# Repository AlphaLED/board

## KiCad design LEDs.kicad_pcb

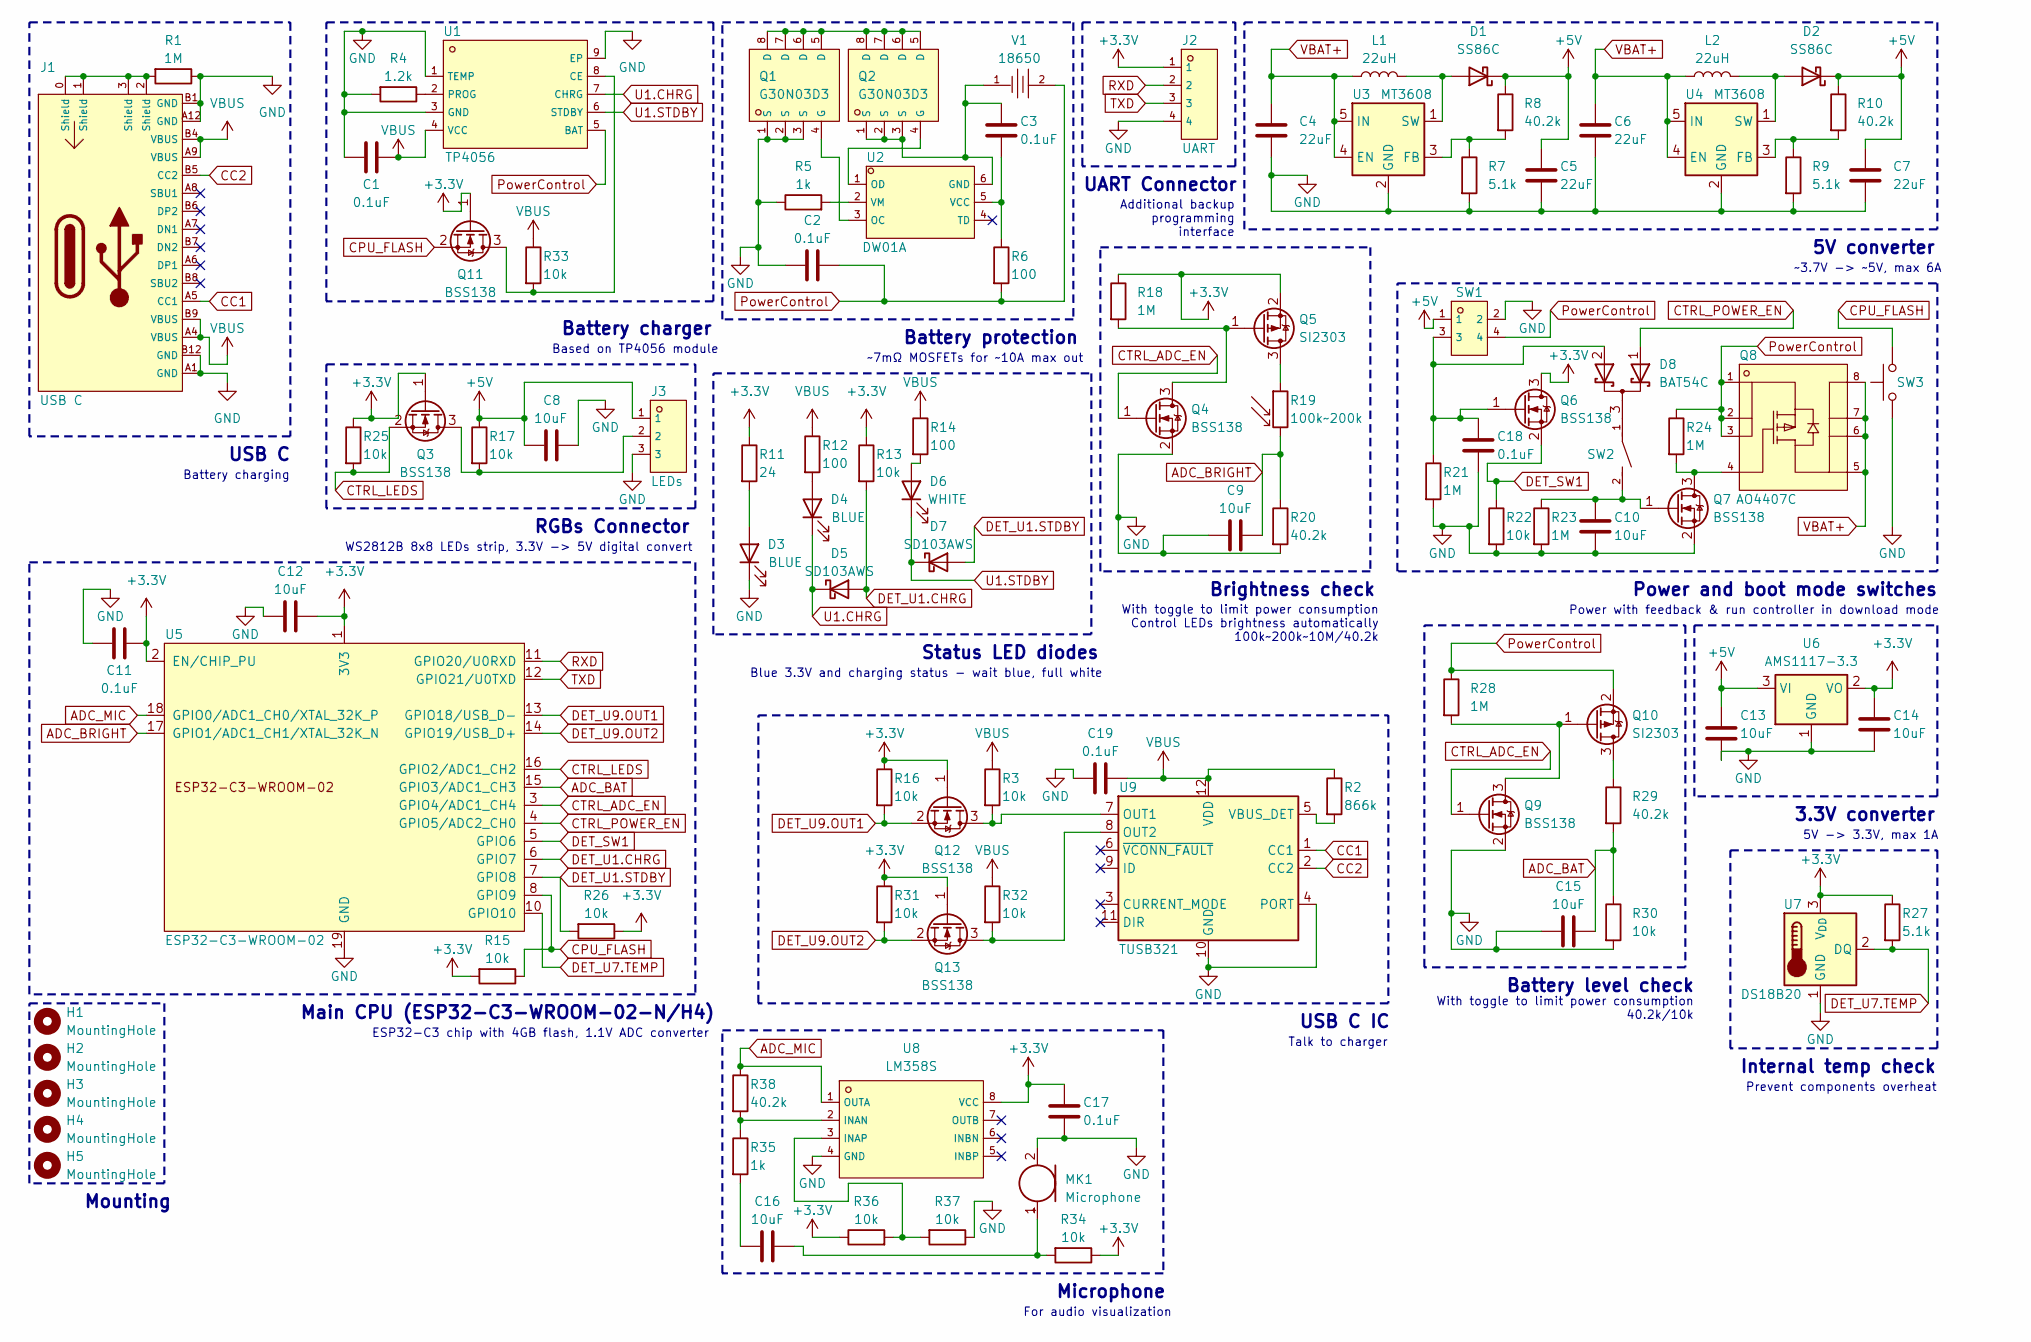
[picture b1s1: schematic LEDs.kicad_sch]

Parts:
C1, C2, C3, C11, C17, C18, C19: 0.1uF; C_0402_1005Metric_Pad0.74x0.62mm_HandSolder; LCSC C344189
C4, C5, C6, C7: 22uF; C_0805_2012Metric_Pad1.18x1.45mm_HandSolder; LCSC C98190
C8, C9, C10, C12, C13, C14, C15, C16: 10uF; C_0805_2012Metric_Pad1.18x1.45mm_HandSolder; LCSC C1713
D1, D2: SS86C; D_SMC_Handsoldering; LCSC C382823
D3, D4: BLUE; LED_0603_1608Metric_Pad1.05x0.95mm_HandSolder; LCSC C965807
D5, D7: SD103AWS; D_SOD-323_HandSoldering; LCSC C513472
D6: WHITE; LED_0603_1608Metric_Pad1.05x0.95mm_HandSolder; LCSC C965808
D8: BAT54C; SOT-23; LCSC C2992451
H1, H2, H3, H4: MountingHole; MountingHole_5.3mm_M5
H5: MountingHole; MountingHole_3.2mm_M3
J1: USB C; USB-C_SMD-TYPE-C-31-M-12; LCSC C2927038
J2: UART; HDR-TH_4P-P2.00-V-M; LCSC C541858
J3: LEDs; HDR-TH_3P-P2.54-V-M-1; LCSC C429954
L1, L2: 22uH; L_Bourns-SRN8040_8x8.15mm; LCSC C2942298
MK1: Microphone; MIC-TH_BD6.0_B6027AP383-056; LCSC C5160215
Q1, Q2: G30N03D3; POWERVDFN-8_L3.2-W3.1-P0.65-LS3.3-BL-1; LCSC C840054
Q3, Q4, Q6, Q7, Q9, Q11, Q12, Q13: BSS138; SOT-23; LCSC C347484
Q5, Q10: SI2303; SOT-23; LCSC C545575
Q8: AO4407C; SOP-8_L4.9-W3.9-P1.27-LS6.0-BL; LCSC C469397
R1, R18, R21, R23, R24, R28: 1M; R_0603_1608Metric_Pad0.98x0.95mm_HandSolder; LCSC C103216
R2: 866k; R_0603_1608Metric_Pad0.98x0.95mm_HandSolder; LCSC C5126056
R3, R13, R15, R16, R17, R22, R25, R26, R30, R31, R32, R33, R34, R36, R37: 10k; R_0603_1608Metric_Pad0.98x0.95mm_HandSolder; LCSC C103210
R4: 1.2k; R_0603_1608Metric_Pad0.98x0.95mm_HandSolder; LCSC C2907081
R5, R35: 1k; R_0603_1608Metric_Pad0.98x0.95mm_HandSolder; LCSC C3016283
R6, R12, R14: 100; R_0603_1608Metric_Pad0.98x0.95mm_HandSolder; LCSC C3017758
R7, R9, R27: 5.1k; R_0603_1608Metric_Pad0.98x0.95mm_HandSolder; LCSC C2907114
R8, R10, R20, R29, R38: 40.2k; R_0603_1608Metric_Pad0.98x0.95mm_HandSolder; LCSC C12447
R11: 24; R_0603_1608Metric_Pad0.98x0.95mm_HandSolder; LCSC C3017772
R19: 100k~200k; R_LDR_5.0x4.1mm_P3mm_Vertical; LCSC C125631
SW1: 4-pin; HDR-TH_4P-P2.00-V-M-R2-C2-S2.00; LCSC C6332216
SW2: SW-TH_KF1001-01P-B0-FL-ON-01B; LCSC C5299502
SW3: SW-TH_4P-L4.5-W4.5-P3.00-LS5.0; LCSC C5359331
U1: TP4056; SOP-8_L4.9-W3.9-P1.27-LS6.0-TL-EP; LCSC C7473158
U2: DW01A; SOT-23-6_L2.9-W1.6-P0.95-LS2.8-BL; LCSC C351410
U3, U4: MT3608; SOT-23-6; LCSC C2932326
U5: ESP32-C3-WROOM-02; LCSC C2944070
U6: AMS1117-3.3; SOT-223-3_TabPin2; LCSC C5181460
U7: DS18B20; TO-92_Inline; LCSC C5379069
U8: LM358S; SOP-8_L4.9-W3.9-P1.27-LS6.0-BL; LCSC C83902
U9: TUSB321; Texas_X2QFN-12_1.6x1.6mm_P0.4mm; LCSC C139392
V1: 18650; BAT-TH_BH-18650-A1AJ005; LCSC C5290176

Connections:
+3.3V: C11.2, C12.2, C14.1, C17.1, J2.1, Q3.1 (G), Q5.2 (S), Q6.3 (D), Q11.1 (G), Q12.1 (G), Q13.1 (G), R11.1, R13.1, R15.2, R16.1, R18.1, R25.1, R26.1, R27.1, R31.1, R34.1, R36.1, U5.1 (3V3), U5.2 (EN/CHIP_PU), U6.2 (VO), U7.3 (V_{DD}), U8.8 (VCC)
+5V: C5.1, C7.1, C8.2, C13.1, D1.1 (K), D2.1 (K), J3.1, R8.1, R10.1, R17.1, SW1.1, U6.3 (VI)
ADC_BAT: C15.2, R29.2, R30.1, U5.15 (GPIO3/ADC1_CH3)
ADC_BRIGHT: C9.2, R19.2, R20.1, U5.17 (GPIO1/ADC1_CH1/XTAL_32K_N)
ADC_MIC: R38.1, U5.18 (GPIO0/ADC1_CH0/XTAL_32K_P), U8.1 (OUTA)
CC1: J1.A5 (CC1), U9.1 (CC1)
CC2: J1.B5 (CC2), U9.2 (CC2)
CTRL_ADC_EN: Q4.1 (G), Q9.1 (G), U5.3 (GPIO4/ADC1_CH4)
CTRL_LEDS: Q3.2 (S), R25.2, U5.16 (GPIO2/ADC1_CH2)
CTRL_POWER_EN: D8.1 (K), U5.4 (GPIO5/ADC2_CH0)
DET_SW1: Q6.2 (S), R22.1, U5.5 (GPIO6)
DET_U1.CHRG: D5.2 (A), R13.2, U5.6 (GPIO7)
DET_U1.STDBY: D7.2 (A), R26.2, U5.7 (GPIO8)
DET_U7.TEMP: R27.2, U5.10 (GPIO10), U7.2 (DQ)
DET_U9.OUT1: Q12.2 (S), R16.2, U5.13 (GPIO18/USB_D-)
DET_U9.OUT2: Q13.2 (S), R31.2, U5.14 (GPIO19/USB_D+)
unnamed: C16.2, R35.2
unnamed: D1.2 (A), L1.2, U3.1 (SW)
unnamed: D2.2 (A), L2.2, U4.1 (SW)
unnamed: D3.2 (A), R11.2
unnamed: D4.2 (A), R12.2
unnamed: D6.2 (A), R14.2
unnamed: D8.3 (A), SW2.1
unnamed: J1.0 (Shield), J1.1 (Shield), J1.2 (Shield), J1.3 (Shield), R1.2
unnamed: C16.1, MK1.1 (+), R34.2
unnamed: Q1.5 (D), Q1.6 (D), Q1.7 (D), Q1.8 (D), Q2.5 (D), Q2.6 (D), Q2.7 (D), Q2.8 (D)
unnamed: Q1.4 (G), U2.3 (OC)
unnamed: Q2.4 (G), U2.1 (OD)
unnamed: J3.2, Q3.3 (D), R17.2
unnamed: Q4.3 (D), Q5.1 (G), R18.2
unnamed: Q5.3 (D), R19.1
unnamed: C18.1, D8.2 (K), Q6.1 (G), R21.1, SW1.3
unnamed: Q7.3 (D), Q8.4 (G), R24.2
unnamed: C10.1, Q7.1 (G), R23.1, SW2.2
unnamed: Q10.3 (D), R29.1
unnamed: Q9.3 (D), Q10.1 (G), R28.2
unnamed: Q11.3 (D), R33.2, U1.8 (CE)
unnamed: Q12.3 (D), R3.2, U9.7 (OUT1)
unnamed: Q13.3 (D), R32.2, U9.8 (OUT2)
unnamed: R4.1, U1.2 (PROG)
unnamed: C3.1, Q2.1 (S), Q2.2 (S), Q2.3 (S), U2.6 (GND), V1.1
unnamed: C3.2, R6.1, U2.5 (VCC)
unnamed: R5.2, U2.2 (VM)
unnamed: R7.1, R8.2, U3.3 (FB)
unnamed: R9.1, R10.2, U4.3 (FB)
unnamed: R35.1, R38.2, U8.2 (INAN)
unnamed: R36.2, R37.2, U8.3 (INAP)
unnamed: R2.2, U9.5 (VBUS_DET)
PowerControl: C2.2, Q8.1 (S), Q8.2 (S), Q8.3 (S), Q10.2 (S), R6.2, R24.1, R28.1, SW1.4, U1.5 (BAT), V1.2
RXD: J2.2, U5.11 (GPIO20/U0RXD)
TXD: J2.3, U5.12 (GPIO21/U0TXD)
U1.CHRG: D4.1 (K), D5.1 (K), U1.7 (CHRG)
U1.STDBY: D6.1 (K), D7.1 (K), U1.6 (STDBY)
VBAT+: C4.1, C6.1, L1.1, L2.1, Q8.5 (D), Q8.6 (D), Q8.7 (D), Q8.8 (D), U3.4 (EN), U3.5 (IN), U4.4 (EN), U4.5 (IN)
VBUS: C1.2, C19.2, J1.A4 (VBUS), J1.A9 (VBUS), J1.B4 (VBUS), J1.B9 (VBUS), R2.1, R3.1, R12.1, R14.1, R32.1, R33.1, U1.4 (VCC), U9.12 (VDD)

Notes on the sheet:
Internal temp check
With toggle to limit power consumption Control LEDs brightness automatically 100k~200k~10M/40.2k
USB C
Battery level check
Prevent components overheat
Power with feedback & run controller in download mode
Main CPU (ESP32-C3-WROOM-02-N/H4)
Brightness check
Microphone
Blue 3.3V and charging status - wait blue, full white
WS2812B 8x8 LEDs strip, 3.3V -> 5V digital convert
3.3V converter
RGBs Connector
Battery protection
Status LED diodes
Talk to charger
5V -> 3.3V, max 1A
Battery charging
~7mΩ MOSFETs for ~10A max out
ESP32-C3 chip with 4GB flash, 1.1V ADC converter
Mounting
USB C IC
Power and boot mode switches
5V converter
Battery charger
Based on TP4056 module
UART Connector
Additional backup programming interface
~3.7V -> ~5V, max 6A
With toggle to limit power consumption 40.2k/10k
For audio visualization

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
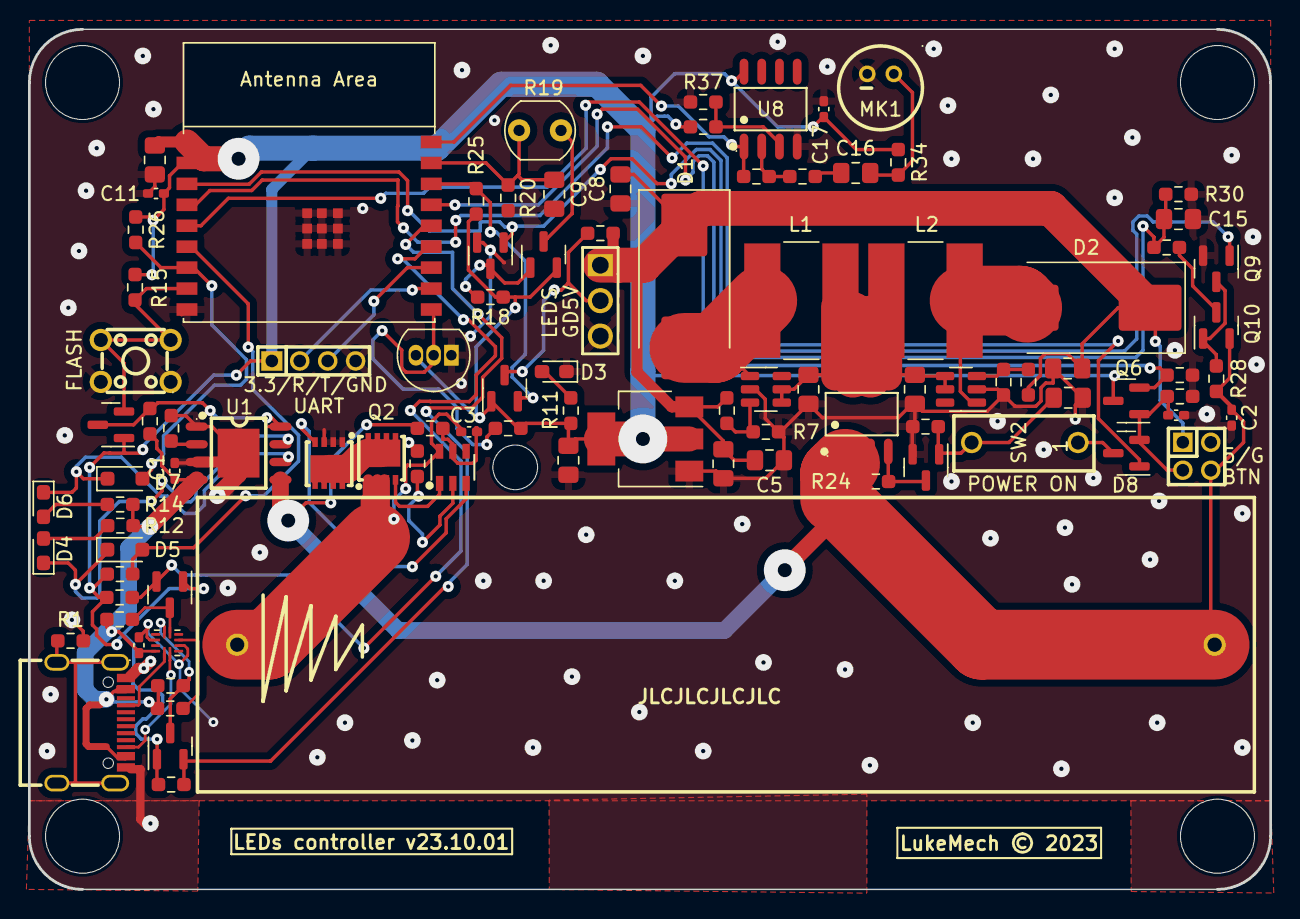
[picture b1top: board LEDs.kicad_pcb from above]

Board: 2 copper layers, 88.9 x 61.6 mm, 102 parts (0 on the bottom side), 57 nets.

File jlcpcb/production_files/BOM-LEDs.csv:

Comment,Designator,Footprint,LCSC
10k,"R13,R15,R16,R17,R22,R25,R26,R3,R30,R31,R32,R33,R34,R36,R37",R_0603_1608Metric_Pad0.98x0.95mm_HandSolder,C103210
1M,"R1,R18,R21,R23,R24,R28",R_0603_1608Metric_Pad0.98x0.95mm_HandSolder,C103216
40.2k,"R10,R20,R29,R38,R8",R_0603_1608Metric_Pad0.98x0.95mm_HandSolder,C12447
100k~200k,R19,R_LDR_5.0x4.1mm_P3mm_Vertical,C125631
TUSB321,U9,Texas_X2QFN-12_1.6x1.6mm_P0.4mm,C139392
10uF,"C10,C12,C13,C14,C15,C16,C8,C9",C_0805_2012Metric_Pad1.18x1.45mm_HandSolder,C1713
1.2k,R4,R_0603_1608Metric_Pad0.98x0.95mm_HandSolder,C2907081
5.1k,"R27,R7,R9",R_0603_1608Metric_Pad0.98x0.95mm_HandSolder,C2907114
USB C,J1,USB-C_SMD-TYPE-C-31-M-12,C2927038
MT3608,"U3,U4",SOT-23-6,C2932326
22uH,"L1,L2",L_Bourns-SRN8040_8x8.15mm,C2942298
ESP32-C3-WROOM-02,U5,ESP32-C3-WROOM-02,C2944070
BAT54C,D8,SOT-23,C2992451
1k,"R35,R5",R_0603_1608Metric_Pad0.98x0.95mm_HandSolder,C3016283
100,"R12,R14,R6",R_0603_1608Metric_Pad0.98x0.95mm_HandSolder,C3017758
24,R11,R_0603_1608Metric_Pad0.98x0.95mm_HandSolder,C3017772
0.1uF,"C1,C11,C17,C18,C19,C2,C3",C_0402_1005Metric_Pad0.74x0.62mm_HandSolder,C344189
BSS138,"Q11,Q12,Q13,Q3,Q4,Q6,Q7,Q9",SOT-23,C347484
DW01A,U2,SOT-23-6_L2.9-W1.6-P0.95-LS2.8-BL,C351410
SS86C,"D1,D2",D_SMC_Handsoldering,C382823
LEDs,J3,HDR-TH_3P-P2.54-V-M-1,C429954
AO4407C,Q8,SOP-8_L4.9-W3.9-P1.27-LS6.0-BL,C469397
866k,R2,R_0603_1608Metric_Pad0.98x0.95mm_HandSolder,C5126056
SD103AWS,"D5,D7",D_SOD-323_HandSoldering,C513472
Microphone,MK1,MIC-TH_BD6.0_B6027AP383-056,C5160215
AMS1117-3.3,U6,SOT-223-3_TabPin2,C5181460
18650,V1,BAT-TH_BH-18650-A1AJ005,C5290176
~,SW2,SW-TH_KF1001-01P-B0-FL-ON-01B,C5299502
~,SW3,SW-TH_4P-L4.5-W4.5-P3.00-LS5.0,C5359331
DS18B20,U7,TO-92_Inline,C5379069
UART,J2,HDR-TH_4P-P2.00-V-M,C541858
SI2303,"Q10,Q5",SOT-23,C545575
4-pin,SW1,HDR-TH_4P-P2.00-V-M-R2-C2-S2.00,C6332216
TP4056,U1,SOP-8_L4.9-W3.9-P1.27-LS6.0-TL-EP,C7473158
LM358S,U8,SOP-8_L4.9-W3.9-P1.27-LS6.0-BL,C83902
G30N03D3,"Q1,Q2",POWERVDFN-8_L3.2-W3.1-P0.65-LS3.3-BL-1,C840054
BLUE,"D3,D4",LED_0603_1608Metric_Pad1.05x0.95mm_HandSolder,C965807
WHITE,D6,LED_0603_1608Metric_Pad1.05x0.95mm_HandSolder,C965808
22uF,"C4,C5,C6,C7",C_0805_2012Metric_Pad1.18x1.45mm_HandSolder,C98190
MountingHole,H1,MountingHole_5.3mm_M5,
MountingHole,H2,MountingHole_5.3mm_M5,
MountingHole,H5,MountingHole_3.2mm_M3,
MountingHole,H4,MountingHole_5.3mm_M5,
MountingHole,H3,MountingHole_5.3mm_M5,

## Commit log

2023-10-01 Modified case design
2023-10-01 Rename board ver, add photos
2023-10-01 Small resistor change

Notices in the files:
LEDs.kicad_pcb:
LukeMech © 2023
